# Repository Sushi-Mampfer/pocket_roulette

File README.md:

# Pocket roulette
A small roulette/dice/rng.

It consists of a 555 that ticks very fast and triggers a 4017 which then triggers the leds one after another, once you let go of the button the 555 stops and the leds stop at wherever they're now. You might be able to time it to land in an area, but I'd be surprised if it was possible to consistently land on the same spot.

# PCB

# Schematic

# Bom
| Reference | Qty | Value |
|----------|-----|-------|
| C2 | 1 | 10u |
| D1-D10 | 10 | LED |
| J1 | 1 | USB_A |
| R1 | 1 | 477 |
| R2 | 1 | 1k |
| R3,R4 | 2 | 500 |
| R5 | 1 | 10k |
| SW1 | 1 | SW_Push |
| U1 | 1 | NE555P |
| U2 | 1 | 4017 |

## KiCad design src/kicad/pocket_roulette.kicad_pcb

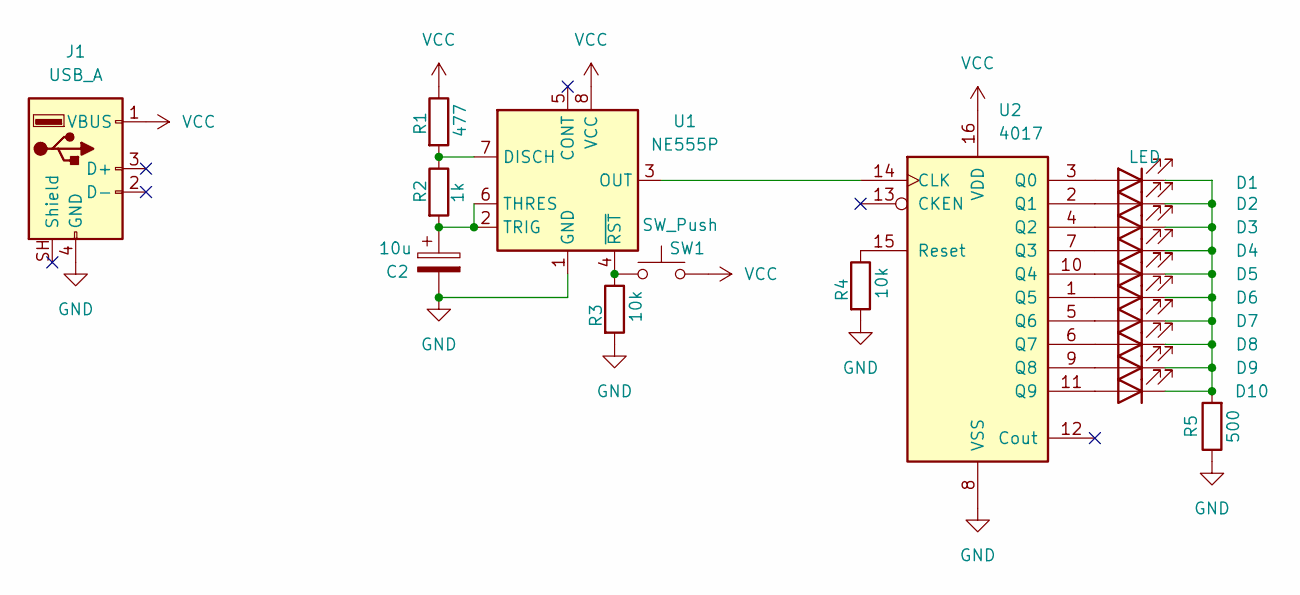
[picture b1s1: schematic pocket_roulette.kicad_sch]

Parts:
C2: 10u; C_Disc_D8.0mm_W5.0mm_P5.00mm
D1, D2, D3, D4, D5, D6, D7, D8, D9, D10: LED; LED_D5.0mm
J1: USB_A; USB_A_Molex_67643_Horizontal
R1: 477; R_Axial_DIN0204_L3.6mm_D1.6mm_P7.62mm_Horizontal
R2: 1k; R_Axial_DIN0204_L3.6mm_D1.6mm_P7.62mm_Horizontal
R3, R4: 10k; R_Axial_DIN0204_L3.6mm_D1.6mm_P7.62mm_Horizontal
R5: 500; R_Axial_DIN0204_L3.6mm_D1.6mm_P7.62mm_Horizontal
SW1: SW_Push; SW_PUSH-12mm
U1: NE555P; DIP-8_W7.62mm
U2: 4017; DIP-16_W7.62mm

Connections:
GND: C2.2, J1.4 (GND), R3.2, R4.2, R5.1, U1.1 (GND), U2.8 (VSS)
unnamed: D1.2 (A), U2.3 (Q0)
unnamed: D1.1 (K), D2.1 (K), D3.1 (K), D4.1 (K), D5.1 (K), D6.1 (K), D7.1 (K), D8.1 (K), D9.1 (K), D10.1 (K), R5.2
unnamed: D2.2 (A), U2.2 (Q1)
unnamed: D3.2 (A), U2.4 (Q2)
unnamed: D4.2 (A), U2.7 (Q3)
unnamed: D5.2 (A), U2.10 (Q4)
unnamed: D6.2 (A), U2.1 (Q5)
unnamed: D7.2 (A), U2.5 (Q6)
unnamed: D8.2 (A), U2.6 (Q7)
unnamed: D9.2 (A), U2.9 (Q8)
unnamed: D10.2 (A), U2.11 (Q9)
unnamed: R1.2, R2.1, U1.7 (DISCH)
unnamed: U1.3 (OUT), U2.14 (CLK)
unnamed: C2.1, R2.2, U1.2 (TRIG), U1.6 (THRES)
unnamed: R3.1, SW1.1, U1.4 (~RST)
unnamed: R4.1, U2.15 (Reset)
VCC: J1.1 (VBUS), R1.1, SW1.2, U1.8 (VCC), U2.16 (VDD)

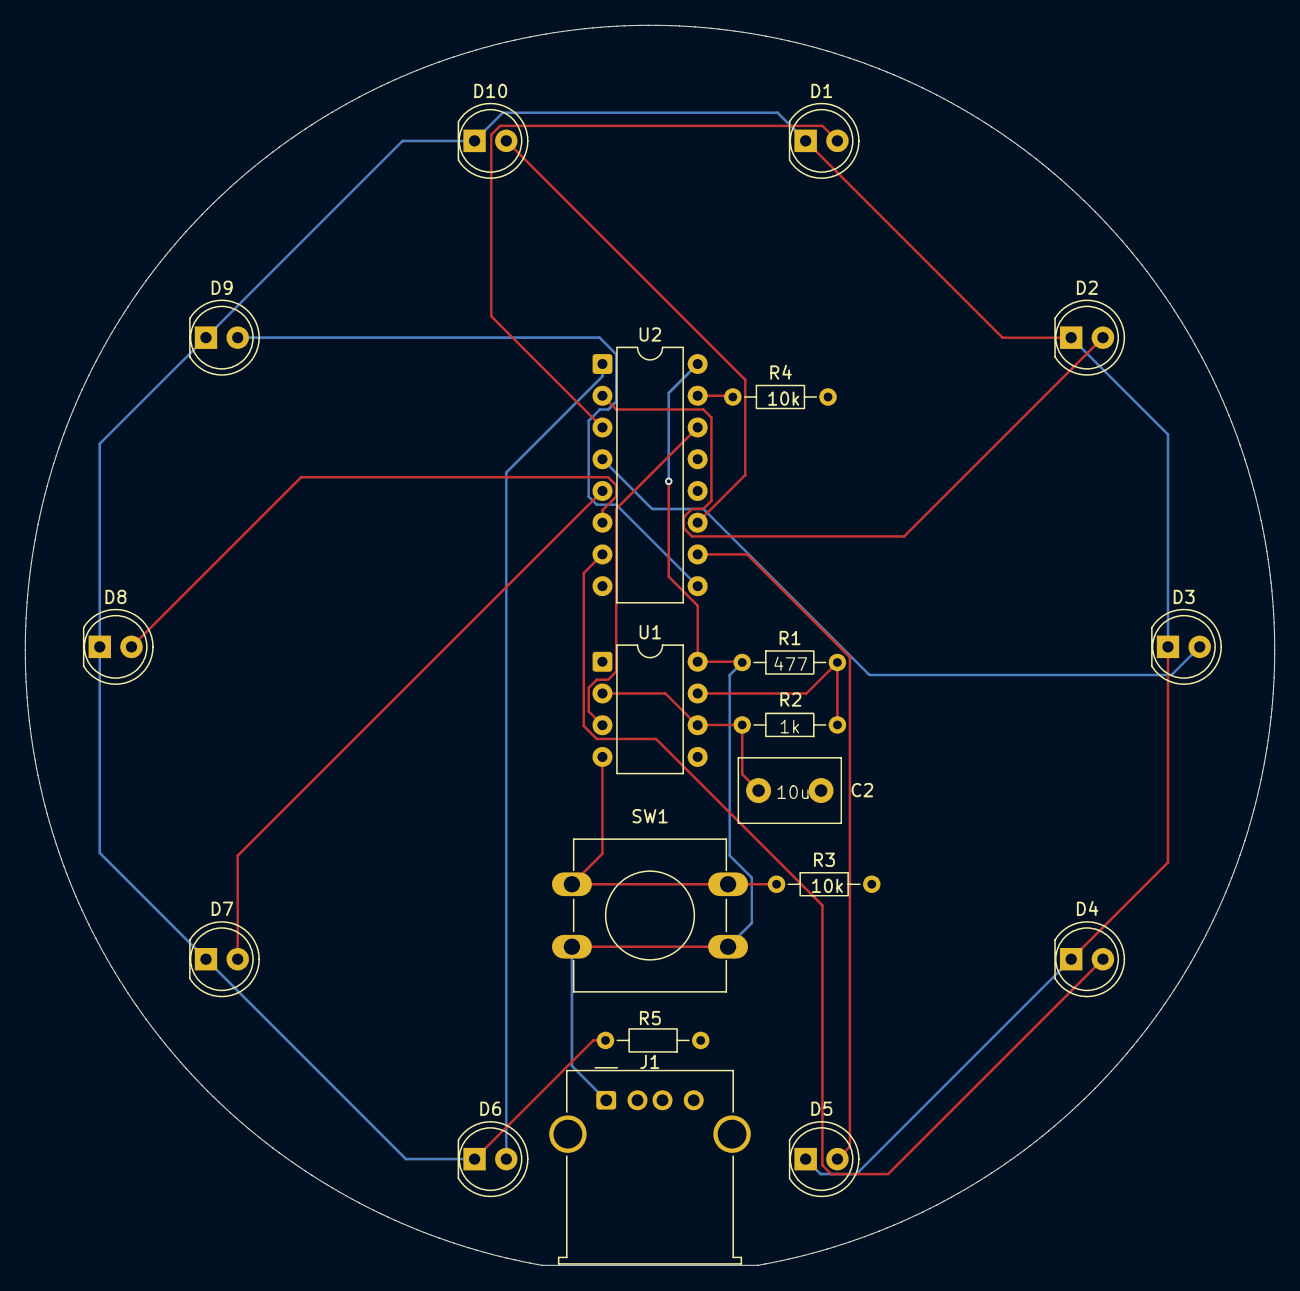
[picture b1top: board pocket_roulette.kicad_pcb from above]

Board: 2 copper layers, 100.0 x 99.3 mm, 20 parts (0 on the bottom side), 18 nets.

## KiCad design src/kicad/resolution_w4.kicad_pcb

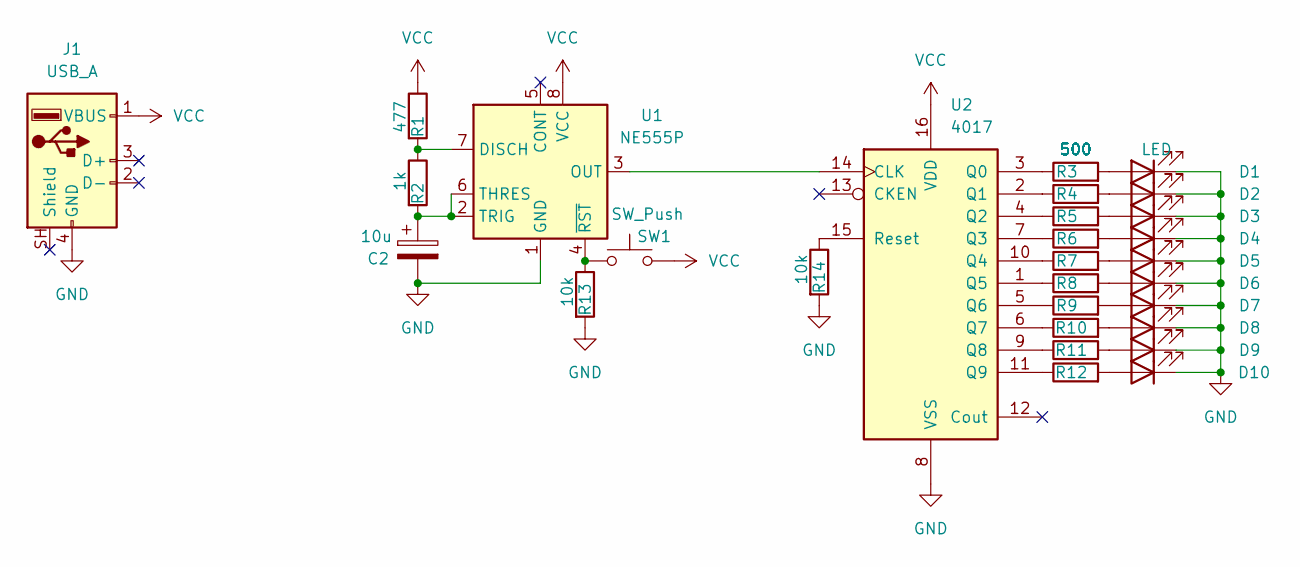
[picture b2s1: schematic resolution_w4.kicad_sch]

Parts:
C2: 10u; C_Disc_D8.0mm_W5.0mm_P5.00mm
D1, D2, D3, D4, D5, D6, D7, D8, D9, D10: LED; LED_D5.0mm
J1: USB_A; USB_A_Molex_67643_Horizontal
R1: 477; R_Axial_DIN0204_L3.6mm_D1.6mm_P7.62mm_Horizontal
R2: 1k; R_Axial_DIN0204_L3.6mm_D1.6mm_P7.62mm_Horizontal
R3, R4, R5, R6, R7, R8, R9, R10, R11, R12: 500; R_Axial_DIN0204_L3.6mm_D1.6mm_P7.62mm_Horizontal
R13, R14: 10k; R_Axial_DIN0204_L3.6mm_D1.6mm_P7.62mm_Horizontal
SW1: SW_Push; SW_PUSH-12mm
U1: NE555P; DIP-8_W7.62mm
U2: 4017; DIP-16_W7.62mm

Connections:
GND: C2.2, D1.1 (K), D2.1 (K), D3.1 (K), D4.1 (K), D5.1 (K), D6.1 (K), D7.1 (K), D8.1 (K), D9.1 (K), D10.1 (K), J1.4 (GND), R13.2, R14.2, U1.1 (GND), U2.8 (VSS)
unnamed: D1.2 (A), R3.2
unnamed: D2.2 (A), R4.2
unnamed: D3.2 (A), R5.2
unnamed: D4.2 (A), R6.2
unnamed: D5.2 (A), R7.2
unnamed: D6.2 (A), R8.2
unnamed: D7.2 (A), R9.2
unnamed: D8.2 (A), R10.2
unnamed: D9.2 (A), R11.2
unnamed: D10.2 (A), R12.2
unnamed: R1.2, R2.1, U1.7 (DISCH)
unnamed: U1.3 (OUT), U2.14 (CLK)
unnamed: C2.1, R2.2, U1.2 (TRIG), U1.6 (THRES)
unnamed: R13.1, SW1.1, U1.4 (~RST)
unnamed: R3.1, U2.3 (Q0)
unnamed: R4.1, U2.2 (Q1)
unnamed: R5.1, U2.4 (Q2)
unnamed: R6.1, U2.7 (Q3)
unnamed: R7.1, U2.10 (Q4)
unnamed: R8.1, U2.1 (Q5)
unnamed: R9.1, U2.5 (Q6)
unnamed: R10.1, U2.6 (Q7)
unnamed: R11.1, U2.9 (Q8)
unnamed: R12.1, U2.11 (Q9)
unnamed: R14.1, U2.15 (Reset)
VCC: J1.1 (VBUS), R1.1, SW1.2, U1.8 (VCC), U2.16 (VDD)

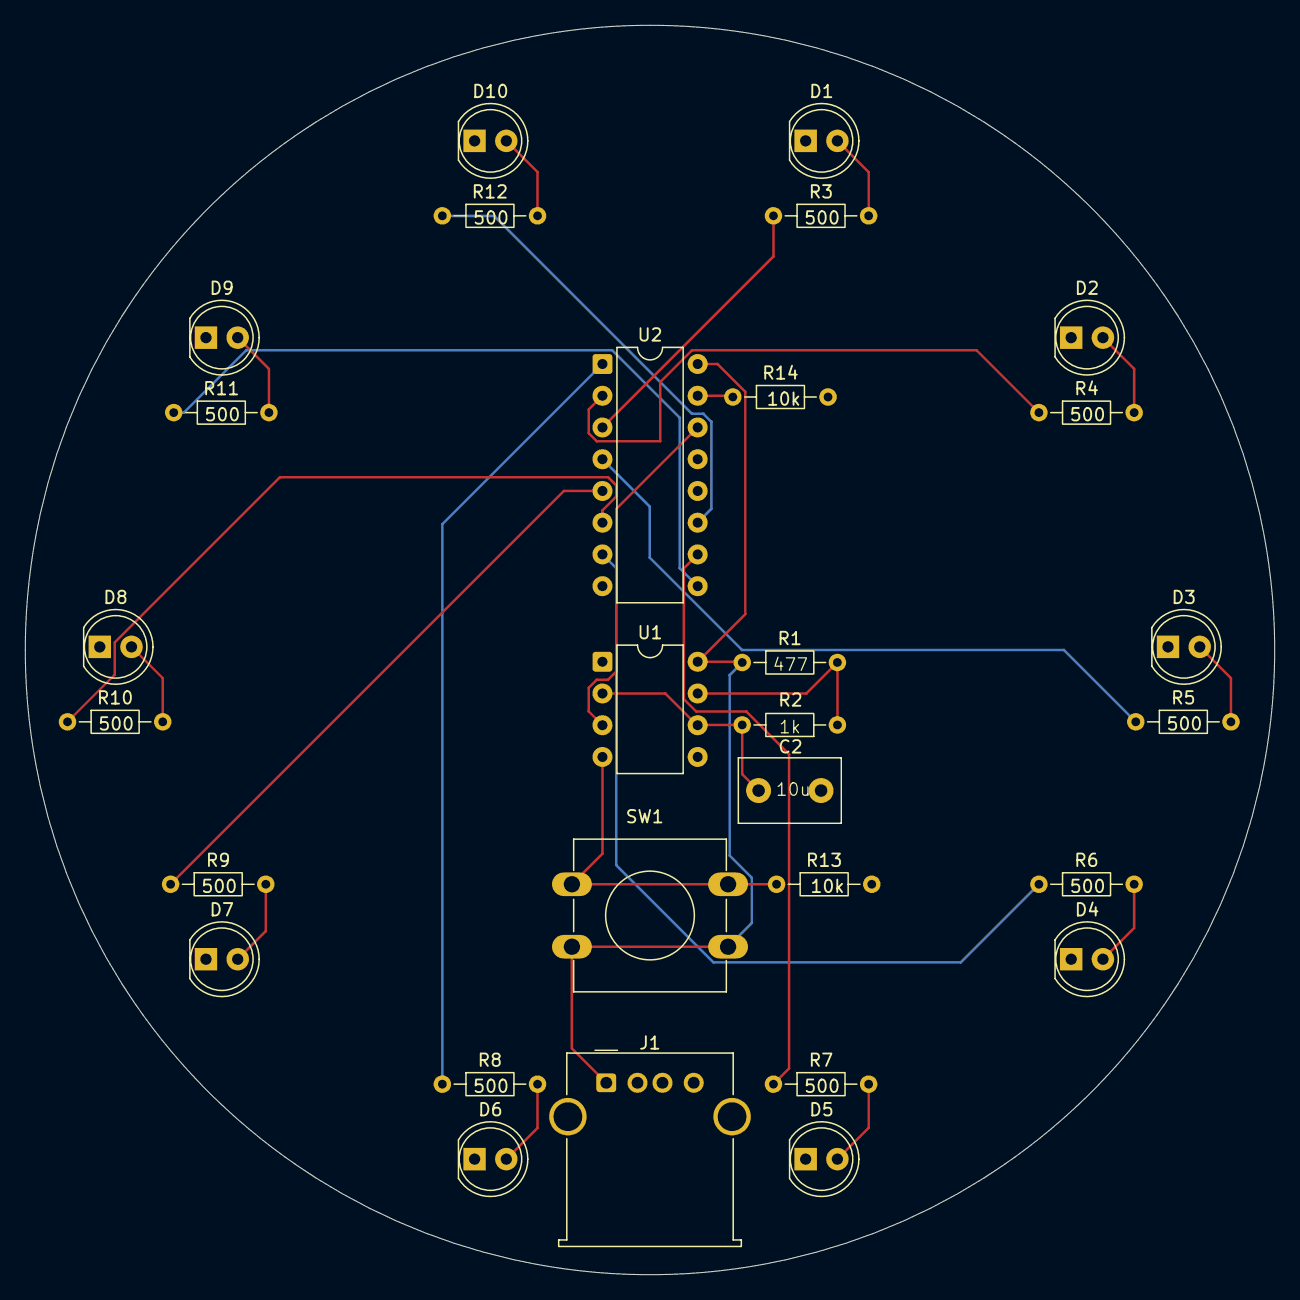
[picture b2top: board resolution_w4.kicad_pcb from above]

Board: 2 copper layers, 100.0 x 100.0 mm, 29 parts (0 on the bottom side), 27 nets.

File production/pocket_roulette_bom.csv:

Designator,Footprint,Quantity,Value,LCSC Part #
C2,C_Disc_D8.0mm_W5.0mm_P5.00mm,1,10u,
"D1, D10, D2, D3, D4, D5, D6, D7, D8, D9",LED_D5.0mm,10,LED,
J1,USB_A_Molex_67643_Horizontal,1,USB_A,
R1,R_Axial_DIN0204_L3.6mm_D1.6mm_P7.62mm_Horizontal,1,477,
"R10, R11, R12, R3, R4, R5, R6, R7, R8, R9",R_Axial_DIN0204_L3.6mm_D1.6mm_P7.62mm_Horizontal,10,500,
"R13, R14",R_Axial_DIN0204_L3.6mm_D1.6mm_P7.62mm_Horizontal,2,10k,
R2,R_Axial_DIN0204_L3.6mm_D1.6mm_P7.62mm_Horizontal,1,1k,
SW1,SW_PUSH-12mm,1,SW_Push,
U1,DIP-8_W7.62mm,1,NE555P,
U2,DIP-16_W7.62mm,1,4017,

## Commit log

2026-04-12 created production dir
2026-04-12 created kicad dir
2026-04-12 Finished readme
2026-04-12 Added journal
2026-04-21 added banner and updated images
2026-04-21 Looks better now
2026-04-21 added reviews
2026-04-22 New version
2026-04-22 review 2
2026-04-22 Create kicad folder
